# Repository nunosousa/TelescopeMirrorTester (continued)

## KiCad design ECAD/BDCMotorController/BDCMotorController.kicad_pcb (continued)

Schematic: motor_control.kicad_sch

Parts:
C61, C62, C63, C64: 100nC; C_0805_2012Metric
R15, R16: 10kR; R_0805_2012Metric
U33: MCP4451; TSSOP-20_4.4x6.5mm_P0.65mm; MPN MCP4451-103E/ST
U34: PCA9555PW; TSSOP-24_4.4x7.8mm_P0.65mm; MPN PCA9555PW,118
U35, U36: MCP6S26; SOIC-14_3.9x8.7mm_P1.27mm; MPN MCP6S26-I/SL

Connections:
+5V: C61.1, C62.1, C63.1, C64.1, R15.1, U33.1 (P3A), U33.10 (P1A), U33.11 (P0A), U33.17 (VDD), U33.20 (P2A), U34.24 (VDD), U35.14 (V_{DD}), U36.14 (V_{DD}); also elsewhere on the board
/ADC conditioning/VA0_IN: U36.1 (V_{OUT}); also elsewhere on the board
/ADC conditioning/VA1_IN: U35.1 (V_{OUT}); also elsewhere on the board
/MCU/INT6: R15.2, U34.1 (~INT); also elsewhere on the board
/MCU/MISO: R16.1; also elsewhere on the board
/MCU/MOSI: U35.11 (SI); also elsewhere on the board
/MCU/SCK: U35.13 (SCK), U36.13 (SCK); also elsewhere on the board
/MCU/SCL: U33.5 (SCL), U34.22 (SCL); also elsewhere on the board
/MCU/SDA: U33.6 (SDA), U34.23 (SDA); also elsewhere on the board
/MCU/~SS: U35.10 (~CS), U36.10 (~CS); also elsewhere on the board
/Motor Control/CURRENT_M1A: U35.2 (CH0), U36.2 (CH0); also elsewhere on the board
/Motor Control/CURRENT_M1B: U35.3 (CH1), U36.3 (CH1); also elsewhere on the board
/Motor Control/CURRENT_M2A: U35.4 (CH2), U36.4 (CH2); also elsewhere on the board
/Motor Control/CURRENT_M2B: U35.5 (CH3), U36.5 (CH3); also elsewhere on the board
/Motor Control/EN_M1A: U34.13 (IO1_0); also elsewhere on the board
/Motor Control/EN_M1B: U34.14 (IO1_1); also elsewhere on the board
/Motor Control/EN_M2A: U34.15 (IO1_2); also elsewhere on the board
/Motor Control/EN_M2B: U34.16 (IO1_3); also elsewhere on the board
/Motor Control/F/~R_MA: U34.19 (IO1_6); also elsewhere on the board
/Motor Control/F/~R_MB: U34.20 (IO1_7); also elsewhere on the board
/Motor Control/LIM_SW00: U34.4 (IO0_0); also elsewhere on the board
/Motor Control/LIM_SW01: U34.5 (IO0_1); also elsewhere on the board
/Motor Control/LIM_SW02: U34.6 (IO0_2); also elsewhere on the board
/Motor Control/LIM_SW03: U34.7 (IO0_3); also elsewhere on the board
/Motor Control/LIM_SW04: U34.8 (IO0_4); also elsewhere on the board
/Motor Control/LIM_SW05: U34.9 (IO0_5); also elsewhere on the board
/Motor Control/POT_~RESET: U33.15 (~RESET), U34.17 (IO1_4)
/Motor Control/VREF_M1A: U33.12 (P0W); also elsewhere on the board
/Motor Control/VREF_M1B: U33.19 (P2W); also elsewhere on the board
/Motor Control/VREF_M2A: U33.2 (P3W); also elsewhere on the board
/Motor Control/VREF_M2B: U33.9 (P1W); also elsewhere on the board
GND: C61.2, C62.2, C63.2, C64.2, R16.2, U33.3 (P3B), U33.4 (HVC/A0), U33.7 (VSS), U33.8 (P1B), U33.13 (P0B), U33.16 (A1), U33.18 (P2B), U34.2 (A1), U34.3 (A2), U34.12 (VSS), U34.21 (A0), U35.6 (CH4), U35.7 (CH5), U35.8 (V_{REF}), U35.9 (GND), U36.6 (CH4), U36.7 (CH5), U36.8 (V_{REF}), U36.9 (GND); also elsewhere on the board
unnamed: U35.12 (SO), U36.11 (SI)

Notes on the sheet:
I2C Address: 0100 000
I2C Address: 0101 100
I/O concentrator
The SO pin on the MCP6S26 is only used for daisy chain multiple such units. No read commans are available, so not useful to connect back to the MCU.

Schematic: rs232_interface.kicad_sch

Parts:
C25: 100nC; C_0805_2012Metric
C26, C27, C28, C29: 330nC; C_0805_2012Metric
U15: SP3243E; TSSOP-28_4.4x9.7mm_P0.65mm; MPN SP3243EBEY-L/TR

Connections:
+5V: C25.1, U15.26 (VCC); also elsewhere on the board
/MCU/RXD1: U15.15 (R5OUT); also elsewhere on the board
/MCU/TXD1: U15.13 (T2IN); also elsewhere on the board
/Serial ports/CTS_IN1: U15.19 (R1OUT); also elsewhere on the board
/Serial ports/CTS_LINE1: U15.4 (R1IN); also elsewhere on the board
/Serial ports/DCD_IN1: U15.17 (R3OUT); also elsewhere on the board
/Serial ports/DCD_LINE1: U15.6 (R3IN); also elsewhere on the board
/Serial ports/DSR_IN1: U15.16 (R4OUT); also elsewhere on the board
/Serial ports/DSR_LINE1: U15.7 (R4IN); also elsewhere on the board
/Serial ports/DTR_IN1: U15.14 (T1IN); also elsewhere on the board
/Serial ports/DTR_LINE1: U15.9 (T1OUT); also elsewhere on the board
/Serial ports/RI_IN1: U15.18 (R2OUT); also elsewhere on the board
/Serial ports/RI_LINE1: U15.5 (R2IN); also elsewhere on the board
/Serial ports/RS232 Interface #1/C1+: C26.1, U15.28 (C1+)
/Serial ports/RS232 Interface #1/C1-: C26.2, U15.24 (C1-)
/Serial ports/RS232 Interface #1/C2+: C28.1, U15.1 (C2+)
/Serial ports/RS232 Interface #1/C2-: C28.2, U15.2 (C2-)
/Serial ports/RS232 Interface #1/V+: C29.1, U15.27 (V+)
/Serial ports/RS232 Interface #1/V-: C27.1, U15.3 (V-)
/Serial ports/RTS_IN1: U15.12 (T3IN); also elsewhere on the board
/Serial ports/RTS_LINE1: U15.11 (T3OUT); also elsewhere on the board
/Serial ports/RX_LINE1: U15.8 (R5IN); also elsewhere on the board
/Serial ports/ST_IN1: U15.21 (~STATUS); also elsewhere on the board
/Serial ports/TX_LINE1: U15.10 (T2OUT); also elsewhere on the board
/Serial ports/~SHDN_IN1: U15.22 (~SHUTDOWN), U15.23 (~ONLINE); also elsewhere on the board
GND: C25.2, C27.2, C29.2, U15.25 (GND); also elsewhere on the board

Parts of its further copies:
C30, C101: 100nC; C_0805_2012Metric
C31, C32, C33, C34, C102, C103, C104, C105: 330nC; C_0805_2012Metric
U16, U51: SP3243E; TSSOP-28_4.4x9.7mm_P0.65mm; MPN SP3243EBEY-L/TR

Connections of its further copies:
+5V: C30.1, C101.1, U16.26 (VCC), U51.26 (VCC); also elsewhere on the board
/MCU/RXD2: U16.15 (R5OUT); also elsewhere on the board
/MCU/RXD3: U51.15 (R5OUT); also elsewhere on the board
/MCU/TXD2: U16.13 (T2IN); also elsewhere on the board
/MCU/TXD3: U51.13 (T2IN); also elsewhere on the board
/Serial ports/CTS_IN2: U16.19 (R1OUT); also elsewhere on the board
/Serial ports/CTS_IN3: U51.19 (R1OUT); also elsewhere on the board
/Serial ports/CTS_LINE2: U16.4 (R1IN); also elsewhere on the board
/Serial ports/CTS_LINE3: U51.4 (R1IN); also elsewhere on the board
/Serial ports/DCD_IN2: U16.17 (R3OUT); also elsewhere on the board
/Serial ports/DCD_IN3: U51.17 (R3OUT); also elsewhere on the board
/Serial ports/DCD_LINE2: U16.6 (R3IN); also elsewhere on the board
/Serial ports/DCD_LINE3: U51.6 (R3IN); also elsewhere on the board
/Serial ports/DSR_IN2: U16.16 (R4OUT); also elsewhere on the board
/Serial ports/DSR_IN3: U51.16 (R4OUT); also elsewhere on the board
/Serial ports/DSR_LINE2: U16.7 (R4IN); also elsewhere on the board
/Serial ports/DSR_LINE3: U51.7 (R4IN); also elsewhere on the board
/Serial ports/DTR_IN2: U16.14 (T1IN); also elsewhere on the board
/Serial ports/DTR_IN3: U51.14 (T1IN); also elsewhere on the board
/Serial ports/DTR_LINE2: U16.9 (T1OUT); also elsewhere on the board
/Serial ports/DTR_LINE3: U51.9 (T1OUT); also elsewhere on the board
/Serial ports/RI_IN2: U16.18 (R2OUT); also elsewhere on the board
/Serial ports/RI_IN3: U51.18 (R2OUT); also elsewhere on the board
/Serial ports/RI_LINE2: U16.5 (R2IN); also elsewhere on the board
/Serial ports/RI_LINE3: U51.5 (R2IN); also elsewhere on the board
/Serial ports/RS232 Interface #2/C1+: C31.1, U16.28 (C1+)
/Serial ports/RS232 Interface #2/C1-: C31.2, U16.24 (C1-)
/Serial ports/RS232 Interface #2/C2+: C33.1, U16.1 (C2+)
/Serial ports/RS232 Interface #2/C2-: C33.2, U16.2 (C2-)
/Serial ports/RS232 Interface #2/V+: C34.1, U16.27 (V+)
/Serial ports/RS232 Interface #2/V-: C32.1, U16.3 (V-)
/Serial ports/RS232 Interface #3/C1+: C102.1, U51.28 (C1+)
/Serial ports/RS232 Interface #3/C1-: C102.2, U51.24 (C1-)
/Serial ports/RS232 Interface #3/C2+: C104.1, U51.1 (C2+)
/Serial ports/RS232 Interface #3/C2-: C104.2, U51.2 (C2-)
/Serial ports/RS232 Interface #3/V+: C105.1, U51.27 (V+)
/Serial ports/RS232 Interface #3/V-: C103.1, U51.3 (V-)
/Serial ports/RTS_IN2: U16.12 (T3IN); also elsewhere on the board
/Serial ports/RTS_IN3: U51.12 (T3IN); also elsewhere on the board
/Serial ports/RTS_LINE2: U16.11 (T3OUT); also elsewhere on the board
/Serial ports/RTS_LINE3: U51.11 (T3OUT); also elsewhere on the board
/Serial ports/RX_LINE2: U16.8 (R5IN); also elsewhere on the board
/Serial ports/RX_LINE3: U51.8 (R5IN); also elsewhere on the board
/Serial ports/ST_IN2: U16.21 (~STATUS); also elsewhere on the board
/Serial ports/ST_IN3: U51.21 (~STATUS); also elsewhere on the board
/Serial ports/TX_LINE2: U16.10 (T2OUT); also elsewhere on the board
/Serial ports/TX_LINE3: U51.10 (T2OUT); also elsewhere on the board
/Serial ports/~SHDN_IN2: U16.22 (~SHUTDOWN), U16.23 (~ONLINE); also elsewhere on the board
/Serial ports/~SHDN_IN3: U51.22 (~SHUTDOWN), U51.23 (~ONLINE); also elsewhere on the board
GND: C30.2, C32.2, C34.2, C101.2, C103.2, C105.2, U16.25 (GND), U51.25 (GND); also elsewhere on the board

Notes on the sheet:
16V

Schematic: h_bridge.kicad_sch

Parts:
C1, C2, C4, C5, C6, C7, C8, C11: 100nC; C_0805_2012Metric
C3, C12: 100pC; C_0805_2012Metric; MPN CC0805KRX7R9BB101
C9: 10uC; C_0805_2012Metric; MPN GRM21BR61E106MA73L
C10: 47uC; C_1210_3225Metric; MPN GRM32ER61C476KE15L
C134: 2.2uC; C_0805_2012Metric
J1: Screw_Terminal_01x06; TerminalBlock_Phoenix_MPT-0,5-6-2.54_1x06_P2.54mm_Horizontal
R1, R3: 1kR; R_0805_2012Metric
R2: 150mR; R_1206_3216Metric; MPN RLH12FTCR150
U1: 74AHC2G125; TSSOP-8_3x3mm_P0.65mm; MPN 74AHC2G125DP,125
U2, U3: 74AHC00; TSSOP-14_4.4x5mm_P0.65mm; MPN SN74AHC00PWR
U4, U6: 74AHC1G17; SC-74A-5_1.55x2.9mm_P0.95mm; MPN 74AHC1G17GVH
U5: DRV8870DDA; Texas_HTSOP-8-1EP_3.9x4.9mm_P1.27mm_EP2.95x4.9mm_Mask2.4x3.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; MPN DRV8870DDAR
U7: INA180A1; SOT-23-5; MPN INA180A1IDBVR

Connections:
+5V: C1.1, C2.1, C4.1, C5.1, C6.1, C11.1, C134.1, J1.3, U1.8 (VCC), U2.14 (VCC), U3.14 (VCC), U4.5 (VCC), U6.5 (VCC), U7.5 (V+); also elsewhere on the board
/MCU/OC1A: U3.2, U3.12; also elsewhere on the board
/MCU/PH4: U1.3; also elsewhere on the board
/MCU/PH5: U1.6; also elsewhere on the board
/Motor Control/CURRENT_M1A: U7.1; also elsewhere on the board
/Motor Control/EN_M1A: U2.5, U2.9, U2.12, U2.13, U3.1, U3.13; also elsewhere on the board
/Motor Control/F/~R_MA: U2.1, U2.2, U2.4; also elsewhere on the board
/Motor Control/H-bridge #1/ENCODER_A_IN: J1.5, R1.2
/Motor Control/H-bridge #1/ENCODER_B_IN: J1.6, R3.2
/Motor Control/H-bridge #1/IN1: U3.6, U5.3 (IN1)
/Motor Control/H-bridge #1/IN2: U3.8, U5.2 (IN2)
/Motor Control/H-bridge #1/MOTOR+: J1.1, U5.6 (OUT1)
/Motor Control/H-bridge #1/MOTOR-: J1.2, U5.8 (OUT2)
/Motor Control/H-bridge #1/~ENABLE_MOTOR: U1.1, U1.7, U2.11
/Motor Control/H-bridge #1/~FORWARD/REVERSE: U2.3, U2.10
/Motor Control/VREF_M1A: C7.1, U5.4 (VREF); also elsewhere on the board
GND: C1.2, C2.2, C3.2, C4.2, C5.2, C6.2, C7.2, C8.2, C9.2, C10.2, C11.2, C12.2, C134.2, J1.4, R2.1, U1.4 (GND), U2.7 (GND), U3.7 (GND), U4.3 (GND), U5.1 (GND), U5.9 (GND), U6.3 (GND), U7.2 (GND), U7.4 (-); also elsewhere on the board
unnamed: C3.1, R1.1, U6.2
unnamed: C12.1, R3.1, U4.2
unnamed: U1.2, U4.4
unnamed: U1.5, U6.4
unnamed: U2.6, U3.4
unnamed: U2.8, U3.10
unnamed: U3.3, U3.5
unnamed: U3.9, U3.11
unnamed: R2.2, U5.7 (ISEN), U7.3 (+)
VDC: C8.1, C9.1, C10.1, U5.5 (VM); also elsewhere on the board

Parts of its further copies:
C13, C14, C16, C17, C18, C19, C20, C23, C35, C36, C38, C39, C40, C41, C42, C45, C47, C48, C50, C51, C52, C53, C54, C57: 100nC; C_0805_2012Metric
C15, C24, C37, C46, C49, C58: 100pC; C_0805_2012Metric; MPN CC0805KRX7R9BB101
C21, C43, C55: 10uC; C_0805_2012Metric; MPN GRM21BR61E106MA73L
C22, C44, C56: 47uC; C_1210_3225Metric; MPN GRM32ER61C476KE15L
C135, C136, C137: 2.2uC; C_0805_2012Metric
J2, J3, J4: Screw_Terminal_01x06; TerminalBlock_Phoenix_MPT-0,5-6-2.54_1x06_P2.54mm_Horizontal
R4, R6, R7, R9, R10, R12: 1kR; R_0805_2012Metric
R5, R8, R11: 150mR; R_1206_3216Metric; MPN RLH12FTCR150
U8, U17, U24: 74AHC2G125; TSSOP-8_3x3mm_P0.65mm; MPN 74AHC2G125DP,125
U9, U10, U18, U19, U25, U26: 74AHC00; TSSOP-14_4.4x5mm_P0.65mm; MPN SN74AHC00PWR
U11, U13, U20, U22, U27, U29: 74AHC1G17; SC-74A-5_1.55x2.9mm_P0.95mm; MPN 74AHC1G17GVH
U12, U21, U28: DRV8870DDA; Texas_HTSOP-8-1EP_3.9x4.9mm_P1.27mm_EP2.95x4.9mm_Mask2.4x3.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; MPN DRV8870DDAR
U14, U23, U30: INA180A1; SOT-23-5; MPN INA180A1IDBVR

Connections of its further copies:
+5V: C13.1, C14.1, C16.1, C17.1, C18.1, C23.1, C35.1, C36.1, C38.1, C39.1, C40.1, C45.1, C47.1, C48.1, C50.1, C51.1, C52.1, C57.1, C135.1, C136.1, C137.1, J2.3, J3.3, J4.3, U8.8 (VCC), U9.14 (VCC), U10.14 (VCC), U11.5 (VCC), U13.5 (VCC), U14.5 (V+), U17.8 (VCC), U18.14 (VCC), U19.14 (VCC), U20.5 (VCC), U22.5 (VCC), U23.5 (V+), U24.8 (VCC), U25.14 (VCC), U26.14 (VCC), U27.5 (VCC), U29.5 (VCC), U30.5 (V+); also elsewhere on the board
/MCU/OC1A: U19.2, U19.12; also elsewhere on the board
/MCU/OC1C: U10.2, U10.12, U26.2, U26.12; also elsewhere on the board
/MCU/PH4: U17.3; also elsewhere on the board
/MCU/PH5: U17.6; also elsewhere on the board
/MCU/PH6: U8.3, U24.3; also elsewhere on the board
/MCU/PH7: U8.6, U24.6; also elsewhere on the board
/Motor Control/CURRENT_M1B: U14.1; also elsewhere on the board
/Motor Control/CURRENT_M2A: U23.1; also elsewhere on the board
/Motor Control/CURRENT_M2B: U30.1; also elsewhere on the board
/Motor Control/EN_M1B: U9.5, U9.9, U9.12, U9.13, U10.1, U10.13; also elsewhere on the board
/Motor Control/EN_M2A: U18.5, U18.9, U18.12, U18.13, U19.1, U19.13; also elsewhere on the board
/Motor Control/EN_M2B: U25.5, U25.9, U25.12, U25.13, U26.1, U26.13; also elsewhere on the board
/Motor Control/F/~R_MA: U18.1, U18.2, U18.4; also elsewhere on the board
/Motor Control/F/~R_MB: U9.1, U9.2, U9.4, U25.1, U25.2, U25.4; also elsewhere on the board
/Motor Control/H-bridge #2/ENCODER_A_IN: J2.5, R4.2
/Motor Control/H-bridge #2/ENCODER_B_IN: J2.6, R6.2
/Motor Control/H-bridge #2/IN1: U10.6, U12.3 (IN1)
/Motor Control/H-bridge #2/IN2: U10.8, U12.2 (IN2)
/Motor Control/H-bridge #2/MOTOR+: J2.1, U12.6 (OUT1)
/Motor Control/H-bridge #2/MOTOR-: J2.2, U12.8 (OUT2)
/Motor Control/H-bridge #2/~ENABLE_MOTOR: U8.1, U8.7, U9.11
/Motor Control/H-bridge #2/~FORWARD/REVERSE: U9.3, U9.10
/Motor Control/H-bridge #3/ENCODER_A_IN: J3.5, R7.2
/Motor Control/H-bridge #3/ENCODER_B_IN: J3.6, R9.2
/Motor Control/H-bridge #3/IN1: U19.6, U21.3 (IN1)
/Motor Control/H-bridge #3/IN2: U19.8, U21.2 (IN2)
/Motor Control/H-bridge #3/MOTOR+: J3.1, U21.6 (OUT1)
/Motor Control/H-bridge #3/MOTOR-: J3.2, U21.8 (OUT2)
/Motor Control/H-bridge #3/~ENABLE_MOTOR: U17.1, U17.7, U18.11
/Motor Control/H-bridge #3/~FORWARD/REVERSE: U18.3, U18.10
/Motor Control/H-bridge #4/ENCODER_A_IN: J4.5, R10.2
/Motor Control/H-bridge #4/ENCODER_B_IN: J4.6, R12.2
/Motor Control/H-bridge #4/IN1: U26.6, U28.3 (IN1)
/Motor Control/H-bridge #4/IN2: U26.8, U28.2 (IN2)
/Motor Control/H-bridge #4/MOTOR+: J4.1, U28.6 (OUT1)
/Motor Control/H-bridge #4/MOTOR-: J4.2, U28.8 (OUT2)
/Motor Control/H-bridge #4/~ENABLE_MOTOR: U24.1, U24.7, U25.11
/Motor Control/H-bridge #4/~FORWARD/REVERSE: U25.3, U25.10
/Motor Control/VREF_M1B: C19.1, U12.4 (VREF); also elsewhere on the board
/Motor Control/VREF_M2A: C41.1, U21.4 (VREF); also elsewhere on the board
/Motor Control/VREF_M2B: C53.1, U28.4 (VREF); also elsewhere on the board
GND: C13.2, C14.2, C15.2, C16.2, C17.2, C18.2, C19.2, C20.2, C21.2, C22.2, C23.2, C24.2, C35.2, C36.2, C37.2, C38.2, C39.2, C40.2, C41.2, C42.2, C43.2, C44.2, C45.2, C46.2, C47.2, C48.2, C49.2, C50.2, C51.2, C52.2, C53.2, C54.2, C55.2, C56.2, C57.2, C58.2, C135.2, C136.2, C137.2, J2.4, J3.4, J4.4, R5.1, R8.1, R11.1, U8.4 (GND), U9.7 (GND), U10.7 (GND), U11.3 (GND), U12.1 (GND), U12.9 (GND), U13.3 (GND), U14.2 (GND), U14.4 (-), U17.4 (GND), U18.7 (GND), U19.7 (GND), U20.3 (GND), U21.1 (GND), U21.9 (GND), U22.3 (GND), U23.2 (GND), U23.4 (-), U24.4 (GND), U25.7 (GND), U26.7 (GND), U27.3 (GND), U28.1 (GND), U28.9 (GND), U29.3 (GND), U30.2 (GND), U30.4 (-); also elsewhere on the board
unnamed: C15.1, R4.1, U13.2
unnamed: C24.1, R6.1, U11.2
unnamed: C37.1, R7.1, U22.2
unnamed: C46.1, R9.1, U20.2
unnamed: C49.1, R10.1, U29.2
unnamed: C58.1, R12.1, U27.2
unnamed: U10.3, U10.5
unnamed: U9.6, U10.4
unnamed: U9.8, U10.10
unnamed: U10.9, U10.11
unnamed: U8.2, U11.4
unnamed: R5.2, U12.7 (ISEN), U14.3 (+)
unnamed: U8.5, U13.4
unnamed: U17.2, U20.4
unnamed: U17.5, U22.4
unnamed: U18.6, U19.4
unnamed: U18.8, U19.10
unnamed: U19.3, U19.5
unnamed: U19.9, U19.11
unnamed: R8.2, U21.7 (ISEN), U23.3 (+)
unnamed: U24.2, U27.4
unnamed: U24.5, U29.4
unnamed: U25.6, U26.4
unnamed: U25.8, U26.10
unnamed: U26.3, U26.5
unnamed: U26.9, U26.11
unnamed: R11.2, U28.7 (ISEN), U30.3 (+)
VDC: C20.1, C21.1, C22.1, C42.1, C43.1, C44.1, C54.1, C55.1, C56.1, U12.5 (VM), U21.5 (VM), U28.5 (VM); also elsewhere on the board

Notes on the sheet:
<- Brake Forward ->
RISEN
H-bridge control logic
ENCODER+
IN2
Input square wave max frequency = 3 kHz (typical hall efect encoder frequency at max motor speed with no load) Low pass filter -3dB Cutoff Frequency: 1,6 MHz
IN1
Current measurement amplifier 20 V/V Gain
ENCODER-
NOT
Encoder inputs low pass filtering
I_trip = VREF/(10*RISEN)
<- Drive Reverse ->
<- Drive Forward ->
A - FORWARD/~{REVERSE} B - ENABLE_MOTOR C - PWM
H-bridge
<- Brake Reverse ->

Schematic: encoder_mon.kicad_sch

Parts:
C112, C115, C116: 100nC; C_0805_2012Metric
C113, C114: 100pC; C_0805_2012Metric; MPN CC0805KRX7R9BB101
R55, R56: 100kR; R_0805_2012Metric; MPN RT0805BRD07100KL
U54, U57, U58: 74AHC00; TSSOP-14_4.4x5mm_P0.65mm; MPN SN74AHC00PWR
U55, U56: 74AHC1G17; SC-74A-5_1.55x2.9mm_P0.95mm; MPN 74AHC1G17GVH

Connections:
+5V: C112.1, C115.1, C116.1, U54.14 (VCC), U55.5 (VCC), U56.5 (VCC), U57.14 (VCC), U58.14 (VCC); also elsewhere on the board
/MCU/INT5: U58.11; also elsewhere on the board
/MCU/PH6: R55.1, U54.1, U54.13; also elsewhere on the board
/MCU/PH7: R56.1, U57.1, U57.13; also elsewhere on the board
GND: C112.2, C113.2, C114.2, C115.2, C116.2, U54.7 (GND), U55.3 (GND), U56.3 (GND), U57.7 (GND), U58.7 (GND), U58.9, U58.10; also elsewhere on the board
unnamed: C113.1, R55.2, U55.2
unnamed: C114.1, R56.2, U56.2
unnamed: U54.2, U54.5, U55.4
unnamed: U54.6, U54.9
unnamed: U54.8, U58.4, U58.5
unnamed: U54.10, U54.11
unnamed: U54.3, U54.4, U54.12
unnamed: U56.4, U57.2, U57.5
unnamed: U57.6, U57.9
unnamed: U57.8, U58.1, U58.2
unnamed: U57.10, U57.11
unnamed: U57.3, U57.4, U57.12
unnamed: U58.6, U58.12
unnamed: U58.3, U58.13

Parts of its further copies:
C124, C130, C132: 100nC; C_0805_2012Metric
C127, C128: 100pC; C_0805_2012Metric; MPN CC0805KRX7R9BB101
R64, R65: 100kR; R_0805_2012Metric; MPN RT0805BRD07100KL
U61, U64, U65: 74AHC00; TSSOP-14_4.4x5mm_P0.65mm; MPN SN74AHC00PWR
U62, U63: 74AHC1G17; SC-74A-5_1.55x2.9mm_P0.95mm; MPN 74AHC1G17GVH

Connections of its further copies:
+5V: C124.1, C130.1, C132.1, U61.14 (VCC), U62.5 (VCC), U63.5 (VCC), U64.14 (VCC), U65.14 (VCC); also elsewhere on the board
/MCU/INT4: U65.11; also elsewhere on the board
/MCU/PH4: R64.1, U61.1, U61.13; also elsewhere on the board
/MCU/PH5: R65.1, U64.1, U64.13; also elsewhere on the board
GND: C124.2, C127.2, C128.2, C130.2, C132.2, U61.7 (GND), U62.3 (GND), U63.3 (GND), U64.7 (GND), U65.7 (GND), U65.9, U65.10; also elsewhere on the board
unnamed: C127.1, R64.2, U62.2
unnamed: C128.1, R65.2, U63.2
unnamed: U61.2, U61.5, U62.4
unnamed: U61.6, U61.9
unnamed: U61.8, U65.4, U65.5
unnamed: U61.10, U61.11
unnamed: U61.3, U61.4, U61.12
unnamed: U63.4, U64.2, U64.5
unnamed: U64.6, U64.9
unnamed: U64.8, U65.1, U65.2
unnamed: U64.10, U64.11
unnamed: U64.3, U64.4, U64.12
unnamed: U65.6, U65.12
unnamed: U65.3, U65.13

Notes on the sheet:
RC filter R = 100kohm +/- 1% C = 100pF +/- 10% tau = 10us +/- 1.1us
1.50V < V_{T-} < 3.05V
tmin = 62.5ns @ fMCU = 16MHz
4.4us < t_{T+} < 13.3us
333us min
Calculated from 74AHC1G17 datasheet
Input encoder signal is a square wave with a max frequency of 3 kHz (hall efect encoder frequency at max motor speed with no load).
Given: - Input encoder maximum frequency - Schmitt trigger (74AHC1G17) parameters - usage of XOR logic gate to generate a pulse for each encoder signal transition an RC filter was chosen such as to produce enough delay to generate a pulse of enough duration for each encoder signal transition as to 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
167us min
XOR gate
Positive going transitions (T+) time intervals calculated in both extreme cases: lowest V_{T+} at fastest tau and highest V_{T+} at slowest tau. Negative going transitions (T-) time intervals calculated in both extreme cases: higest V_{T-} at fastest tau and lowest V_{T-} at slowest tau.
1.95V < V_{T+} < 3.49V
Encoder square wave signal through RC filter
OR gate
Schmitt trigger output waveform RC filtered encoder signal
XOR result between original encoder signal and delayed RC filtered signal
4.4us < t_{T-} < 13.4us

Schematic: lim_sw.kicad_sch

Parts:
C65, C66, C67, C68, C69, C70, C71, C72, C73, C74, C75, C76: 100nC; C_0805_2012Metric
J8, J9: Screw_Terminal_01x06; TerminalBlock_Phoenix_MPT-0,5-6-2.54_1x06_P2.54mm_Horizontal
R17, R18, R19, R20, R21, R22, R23, R24, R25, R26, R27, R28: 10kR; R_0805_2012Metric
U37, U38, U39, U40, U41, U42: 74AHC1G17; SC-74A-5_1.55x2.9mm_P0.95mm; MPN 74AHC1G17GVH

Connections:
+5V: C65.1, C66.1, C67.1, C71.1, C72.1, C73.1, R20.2, R21.2, R22.2, R26.2, R27.2, R28.2, U37.5 (VCC), U38.5 (VCC), U39.5 (VCC), U40.5 (VCC), U41.5 (VCC), U42.5 (VCC); also elsewhere on the board
/Motor Control/LIM_SW00: U37.4; also elsewhere on the board
/Motor Control/LIM_SW01: U38.4; also elsewhere on the board
/Motor Control/LIM_SW02: U39.4; also elsewhere on the board
/Motor Control/LIM_SW03: U40.4; also elsewhere on the board
/Motor Control/LIM_SW04: U41.4; also elsewhere on the board
/Motor Control/LIM_SW05: U42.4; also elsewhere on the board
/Motor Control/Limit Switches/LIM1: J8.1, R17.2, R20.1
/Motor Control/Limit Switches/LIM2: J8.3, R18.2, R21.1
/Motor Control/Limit Switches/LIM3: J8.5, R19.2, R22.1
/Motor Control/Limit Switches/LIM4: J9.1, R23.2, R26.1
/Motor Control/Limit Switches/LIM5: J9.3, R24.2, R27.1
/Motor Control/Limit Switches/LIM6: J9.5, R25.2, R28.1
GND: C65.2, C66.2, C67.2, C68.2, C69.2, C70.2, C71.2, C72.2, C73.2, C74.2, C75.2, C76.2, J8.2, J8.4, J8.6, J9.2, J9.4, J9.6, U37.3 (GND), U38.3 (GND), U39.3 (GND), U40.3 (GND), U41.3 (GND), U42.3 (GND); also elsewhere on the board
unnamed: C68.1, R17.1, U37.2
unnamed: C69.1, R18.1, U38.2
unnamed: C70.1, R19.1, U39.2
unnamed: C74.1, R23.1, U40.2
unnamed: C75.1, R24.1, U41.2
unnamed: C76.1, R25.1, U42.2

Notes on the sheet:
Limit switches debouncing

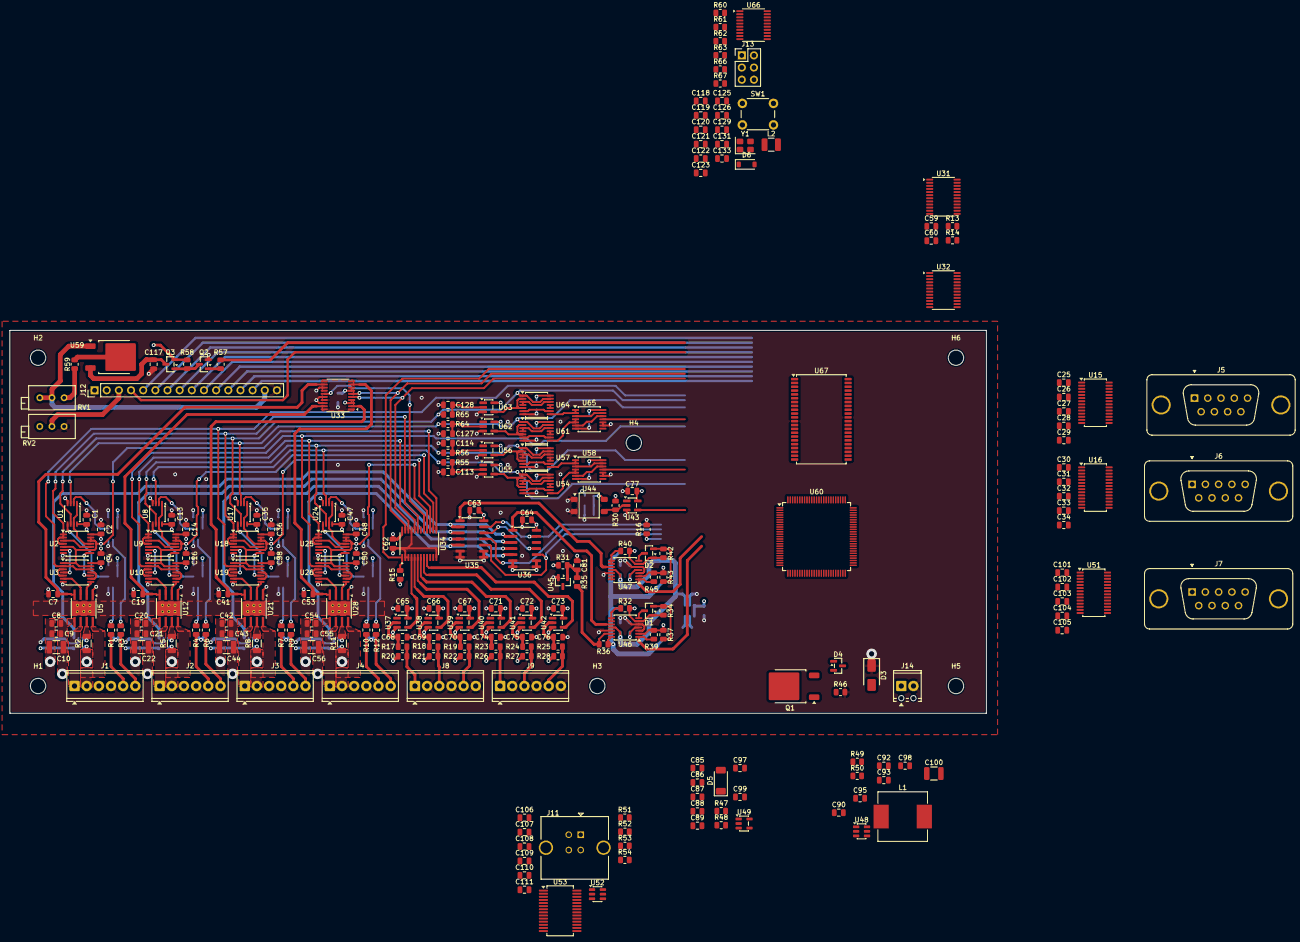
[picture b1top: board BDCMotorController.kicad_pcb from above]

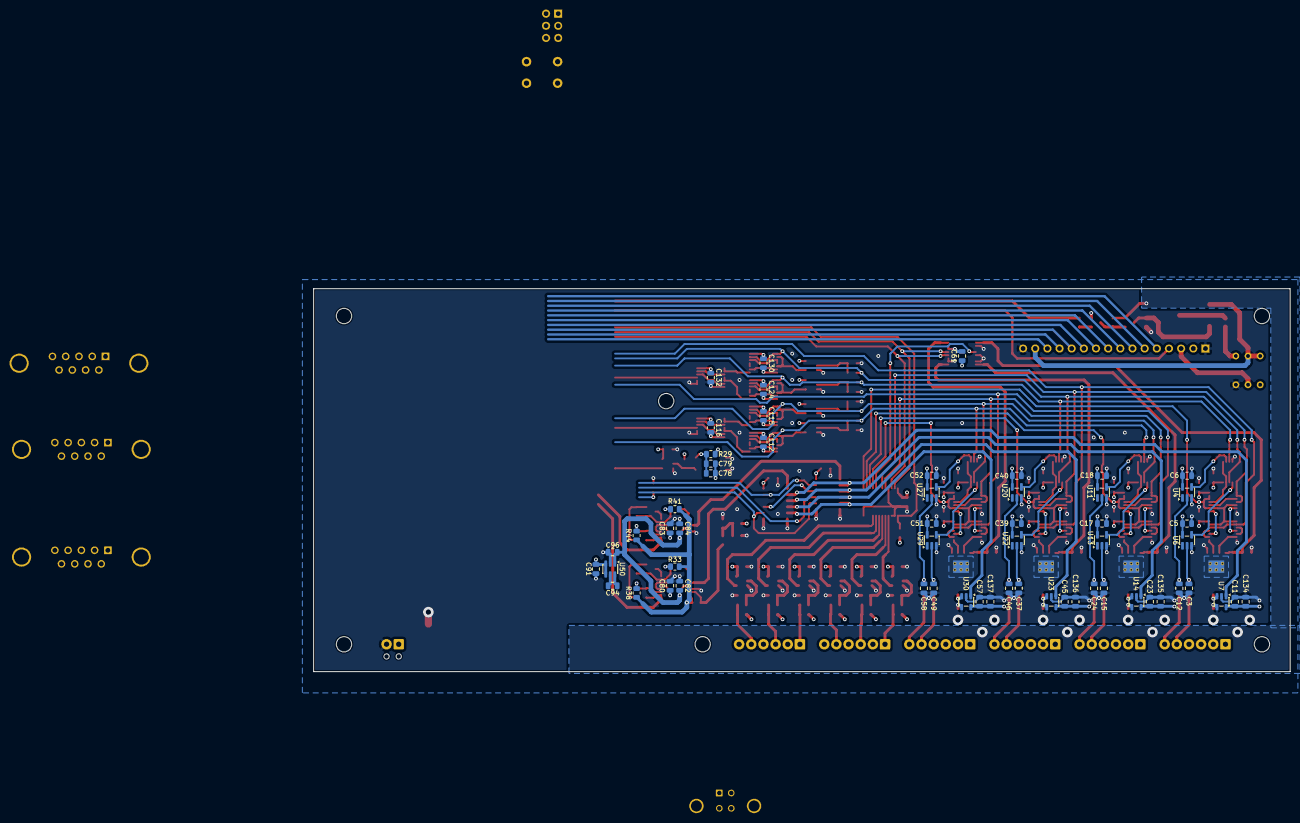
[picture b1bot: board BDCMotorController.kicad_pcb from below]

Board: 4 copper layers, 204.0 x 80.0 mm, 305 parts (58 on the bottom side), 318 nets.

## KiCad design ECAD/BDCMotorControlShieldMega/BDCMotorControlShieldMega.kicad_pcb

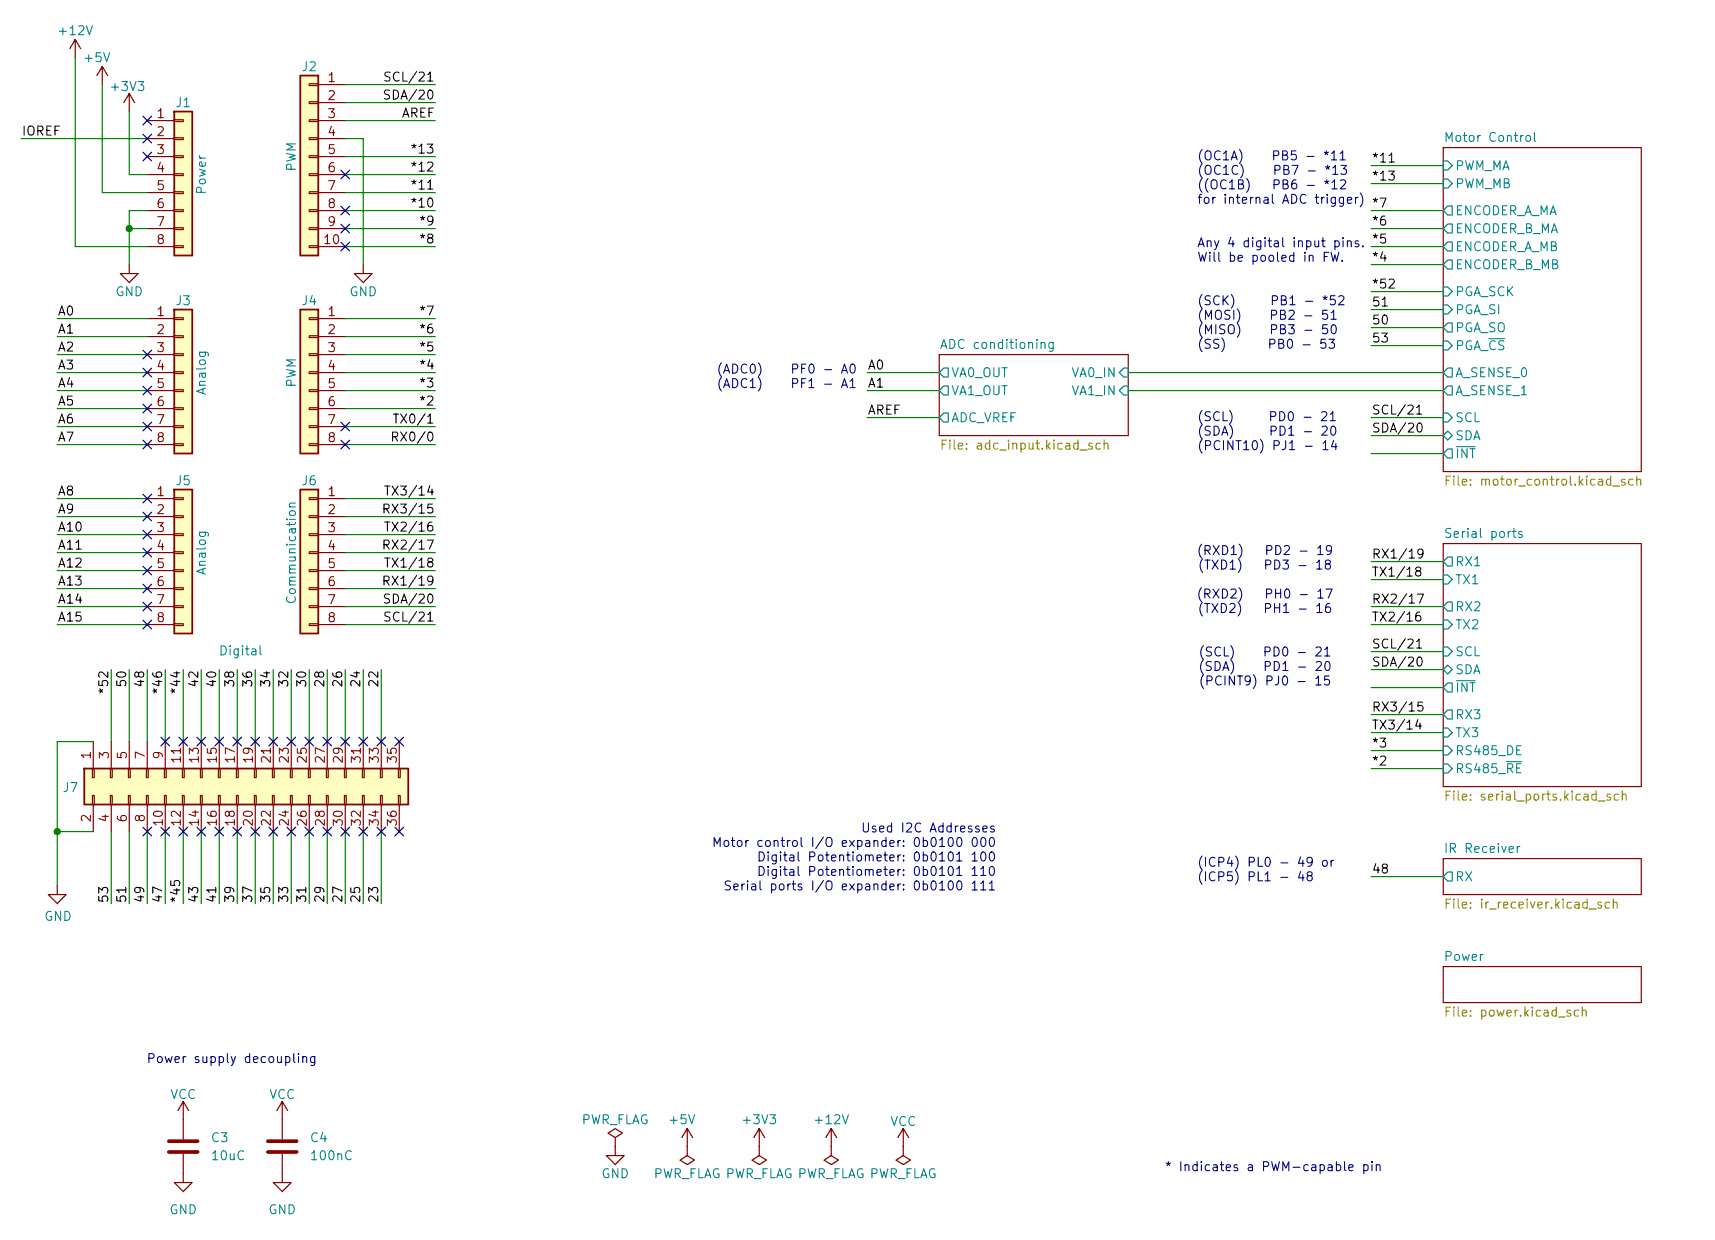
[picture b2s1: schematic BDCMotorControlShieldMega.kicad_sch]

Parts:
C3: 10uC; C_1210_3225Metric; MPN UMK325AB7106KM-T
C4: 100nC; C_0805_2012Metric
J1: Power; PinSocket_1x08_P2.54mm_Vertical; MPN PZ254-1-08-Z-8.5
J2: PWM; PinSocket_1x10_P2.54mm_Vertical; MPN PZ254-1-10-Z-8.5
J3, J5: Analog; PinSocket_1x08_P2.54mm_Vertical; MPN PZ254-1-08-Z-8.5
J4: PWM; PinSocket_1x08_P2.54mm_Vertical; MPN PZ254-1-08-Z-8.5
J6: Communication; PinSocket_1x08_P2.54mm_Vertical; MPN PZ254-1-08-Z-8.5
J7: Digital; PinSocket_2x18_P2.54mm_Vertical; MPN PZ254-2-18-Z-8.5

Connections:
+3V3: J1.4; also elsewhere on the board
+5V: J1.5; also elsewhere on the board
+12V: J1.8; also elsewhere on the board
/22: J7.33
/23: J7.34
/24: J7.31
/25: J7.32
/26: J7.29
/27: J7.30
/28: J7.27
/29: J7.28
/30: J7.25
/31: J7.26
/32: J7.23
/33: J7.24
/34: J7.21
/35: J7.22
/36: J7.19
/37: J7.20
/38: J7.17
/39: J7.18
/40: J7.15
/41: J7.16
/42: J7.13
/43: J7.14
/47: J7.10
/48: J7.7; also elsewhere on the board
/49: J7.8
/50: J7.5; also elsewhere on the board
/51: J7.6; also elsewhere on the board
/53: J7.4; also elsewhere on the board
/*2: J4.6; also elsewhere on the board
/*3: J4.5; also elsewhere on the board
/*4: J4.4; also elsewhere on the board
/*5: J4.3; also elsewhere on the board
/*6: J4.2; also elsewhere on the board
/*7: J4.1; also elsewhere on the board
/*8: J2.10
/*9: J2.9
/*10: J2.8
/*11: J2.7; also elsewhere on the board
/*12: J2.6
/*13: J2.5; also elsewhere on the board
/*44: J7.11
/*45: J7.12
/*46: J7.9
/*52: J7.3; also elsewhere on the board
/A0: J3.1; also elsewhere on the board
/A1: J3.2; also elsewhere on the board
/A2: J3.3
/A3: J3.4
/A4: J3.5
/A5: J3.6
/A6: J3.7
/A7: J3.8
/A8: J5.1
/A9: J5.2
/A10: J5.3
/A11: J5.4
/A12: J5.5
/A13: J5.6
/A14: J5.7
/A15: J5.8
/AREF: J2.3; also elsewhere on the board
/IOREF: J1.2
/RX0/0: J4.8
/RX1/19: J6.6; also elsewhere on the board
/RX2/17: J6.4; also elsewhere on the board
/RX3/15: J6.2; also elsewhere on the board
/SCL/21: J2.1, J6.8; also elsewhere on the board
/SDA/20: J2.2, J6.7; also elsewhere on the board
/TX0/1: J4.7
/TX1/18: J6.5; also elsewhere on the board
/TX2/16: J6.3; also elsewhere on the board
/TX3/14: J6.1; also elsewhere on the board
GND: C3.2, C4.2, J1.6, J1.7, J2.4, J7.1, J7.2; also elsewhere on the board
VCC: C3.1, C4.1; also elsewhere on the board

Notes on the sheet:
Used I2C Addresses Motor control I/O expander: 0b0100 000 Digital Potentiometer: 0b0101 100 Digital Potentiometer: 0b0101 110 Serial ports I/O expander: 0b0100 111
(ADC0) PF0 - A0 (ADC1) PF1 - A1
(ICP4) PL0 - 49 or (ICP5) PL1 - 48
(RXD1) PD2 - 19 (TXD1) PD3 - 18 (RXD2) PH0 - 17 (TXD2) PH1 - 16 (SCL) PD0 - 21 (SDA) PD1 - 20 (PCINT9) PJ0 - 15
Power supply decoupling
* Indicates a PWM-capable pin
(OC1A) PB5 - *11 (OC1C) PB7 - *13 ((OC1B) PB6 - *12 for internal ADC trigger) Any 4 digital input pins. Will be pooled in FW. (SCK) PB1 - *52 (MOSI) PB2 - 51 (MISO) PB3 - 50 (SS) PB0 - 53 (SCL) PD0 - 21 (SDA) PD1 - 20 (PCINT10) PJ1 - 14

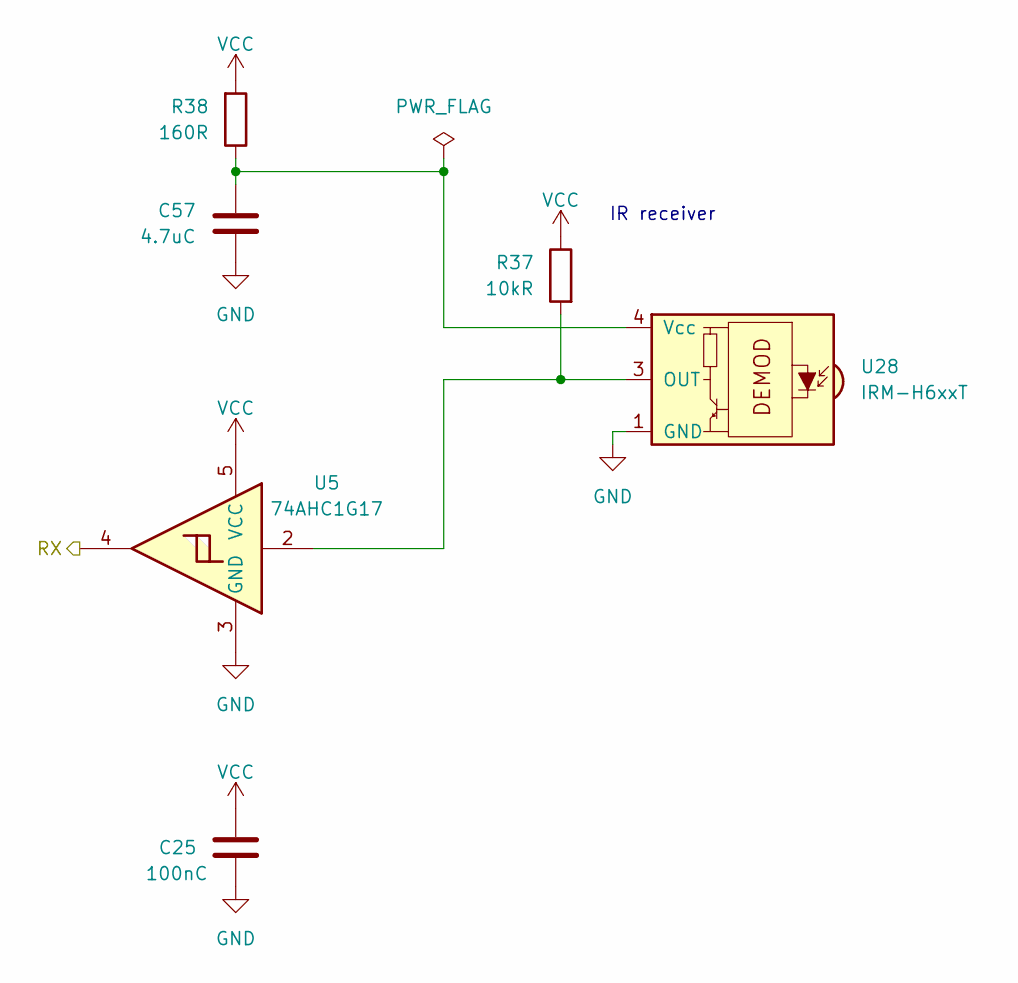
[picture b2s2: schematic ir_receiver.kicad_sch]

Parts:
C25: 100nC; C_0805_2012Metric
C57: 4.7uC; C_0805_2012Metric; MPN CC0805KKX7R8BB475
R37: 10kR; R_0805_2012Metric; MPN RC0805JR-0710KL
R38: 160R; R_0805_2012Metric; MPN AC0805FR-7W160RL
U5: 74AHC1G17; SC-74A-5_1.55x2.9mm_P0.95mm; MPN 74AHC1G17GVH
U28: IRM-H6xxT; Everlight_IRM-H6xxT; MPN IRM-H638J7/TR2(CLW)

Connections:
/48: U5.4; also elsewhere on the board
GND: C25.2, C57.2, U5.3 (GND), U28.1 (GND), U28.2 (GND); also elsewhere on the board
unnamed: R37.2, U5.2, U28.3 (OUT)
unnamed: C57.1, R38.1, U28.4 (Vcc)
VCC: C25.1, R37.1, R38.2, U5.5 (VCC); also elsewhere on the board

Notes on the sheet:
IR receiver
